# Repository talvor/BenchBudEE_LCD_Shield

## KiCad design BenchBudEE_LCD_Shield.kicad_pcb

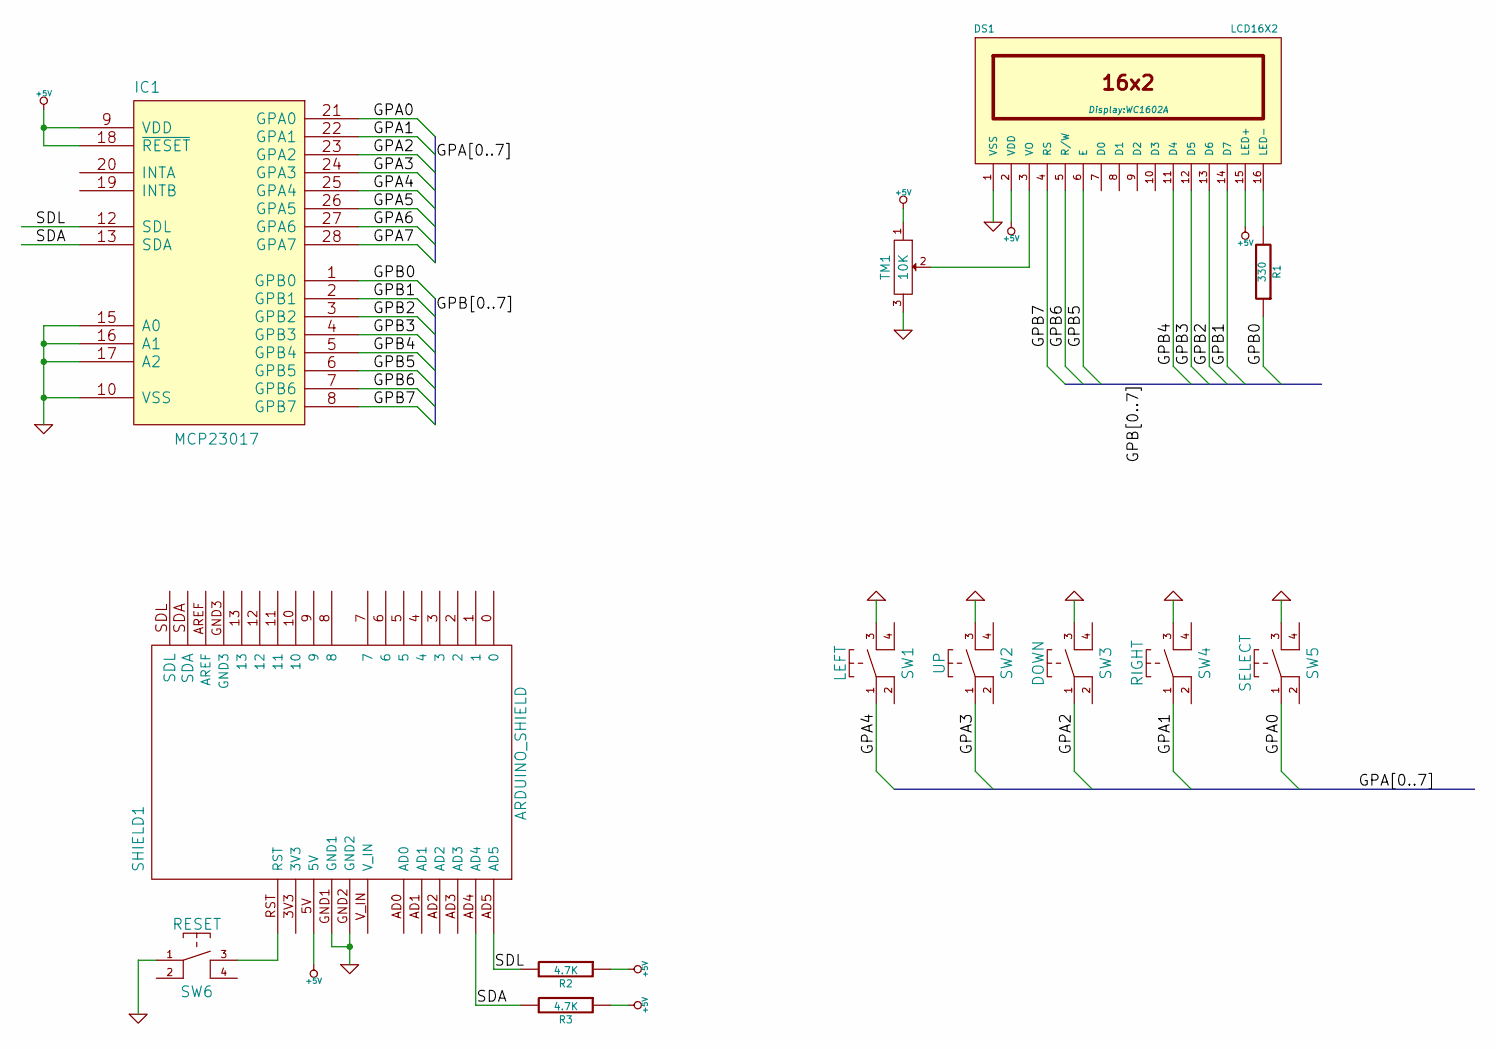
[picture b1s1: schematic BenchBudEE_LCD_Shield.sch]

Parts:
DS1: LCD16X2; WC1602A
IC1: MCP23017; SSOP-28; MFG Part Number MCP23017-E/SS
R1: 330; Resistor_SMD0805_HandSoldering
R2, R3: 4.7K; Resistor_SMD0805_HandSoldering
SHIELD1: ARDUINO_SHIELD; ARDUINO_UNO
SW1: LEFT; SW_PUSH; MFG Part Number MCDTS6-3R
SW2: UP; SW_PUSH; MFG Part Number MCDTS6-3R
SW3: DOWN; SW_PUSH; MFG Part Number MCDTS6-3R
SW4: RIGHT; SW_PUSH; MFG Part Number MCDTS6-3R
SW5: SELECT; SW_PUSH
SW6: RESET; SW_PUSH; MFG Part Number MCDTS6-3R
TM1: 10K; Potentiometer_VishaySpectrol-Econtrim-Type36k; MFG Part Number 3306P-1-103

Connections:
+5V: DS1.2 (VDD), DS1.15 (LED+), IC1.9 (VDD), IC1.18 (~RESET), R2.1, R3.1, SHIELD1.5V, TM1.1
/GPA0: IC1.21 (GPA0), SW5.1
/GPA1: IC1.22 (GPA1), SW4.1
/GPA2: IC1.23 (GPA2), SW3.1
/GPA3: IC1.24 (GPA3), SW2.1
/GPA4: IC1.25 (GPA4), SW1.1
/GPA5: IC1.26 (GPA5)
/GPA6: IC1.27 (GPA6)
/GPA7: IC1.28 (GPA7)
/GPB0: IC1.1 (GPB0), R1.1
/GPB1: DS1.14 (D7), IC1.2 (GPB1)
/GPB2: DS1.13 (D6), IC1.3 (GPB2)
/GPB3: DS1.12 (D5), IC1.4 (GPB3)
/GPB4: DS1.11 (D4), IC1.5 (GPB4)
/GPB5: DS1.6 (E), IC1.6 (GPB5)
/GPB6: DS1.5 (R/W), IC1.7 (GPB6)
/GPB7: DS1.4 (RS), IC1.8 (GPB7)
/SDA: IC1.13 (SDA), R3.2, SHIELD1.AD4
/SDL: IC1.12 (SDL), R2.2, SHIELD1.AD5
GND: DS1.1 (VSS), IC1.10 (VSS), IC1.15 (A0), IC1.16 (A1), IC1.17 (A2), SHIELD1.GND1, SHIELD1.GND2, SW1.3, SW2.3, SW3.3, SW4.3, SW5.3, SW6.1, TM1.3
unnamed: DS1.3 (VO), TM1.2
unnamed: DS1.16 (LED-), R1.2
unnamed: SHIELD1.RST, SW6.3

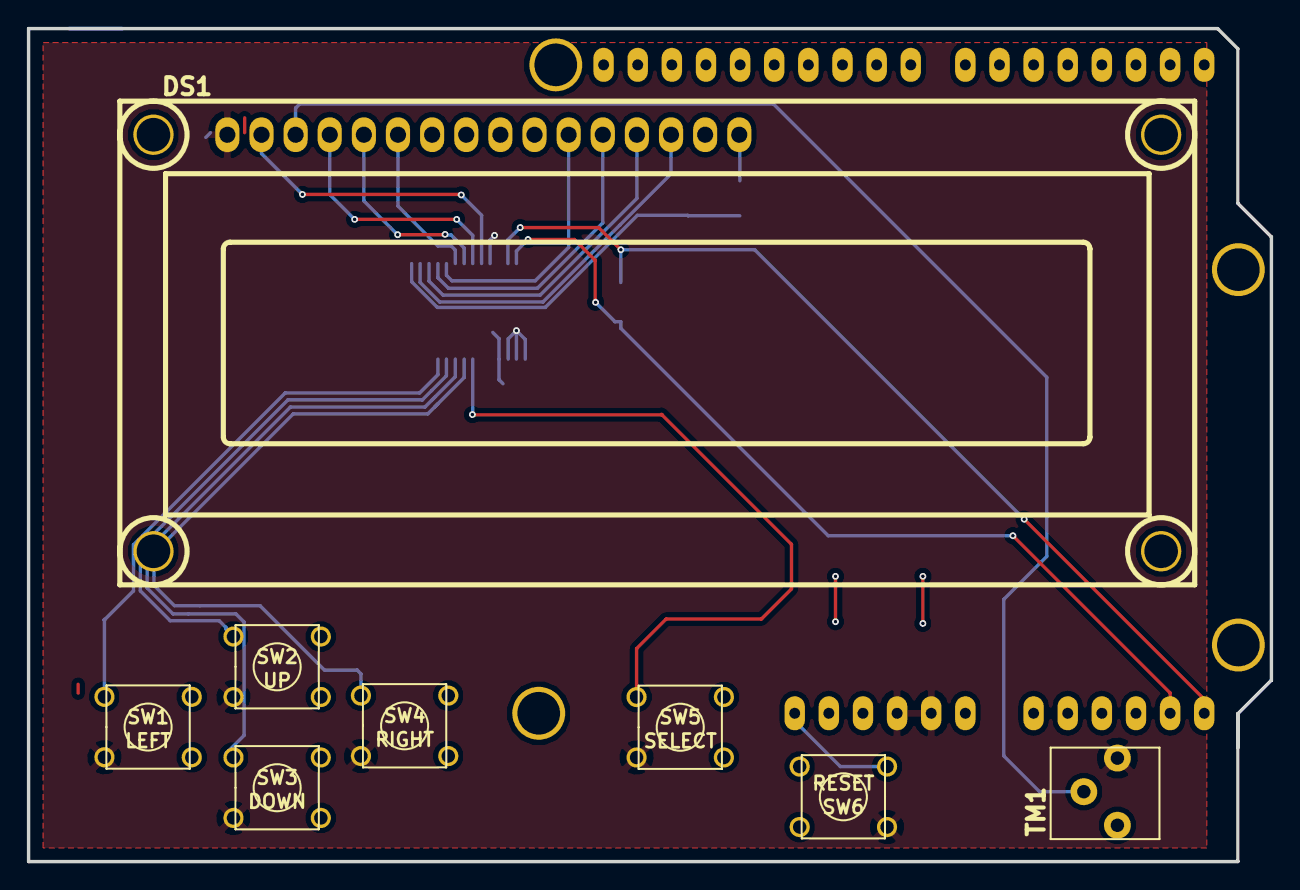
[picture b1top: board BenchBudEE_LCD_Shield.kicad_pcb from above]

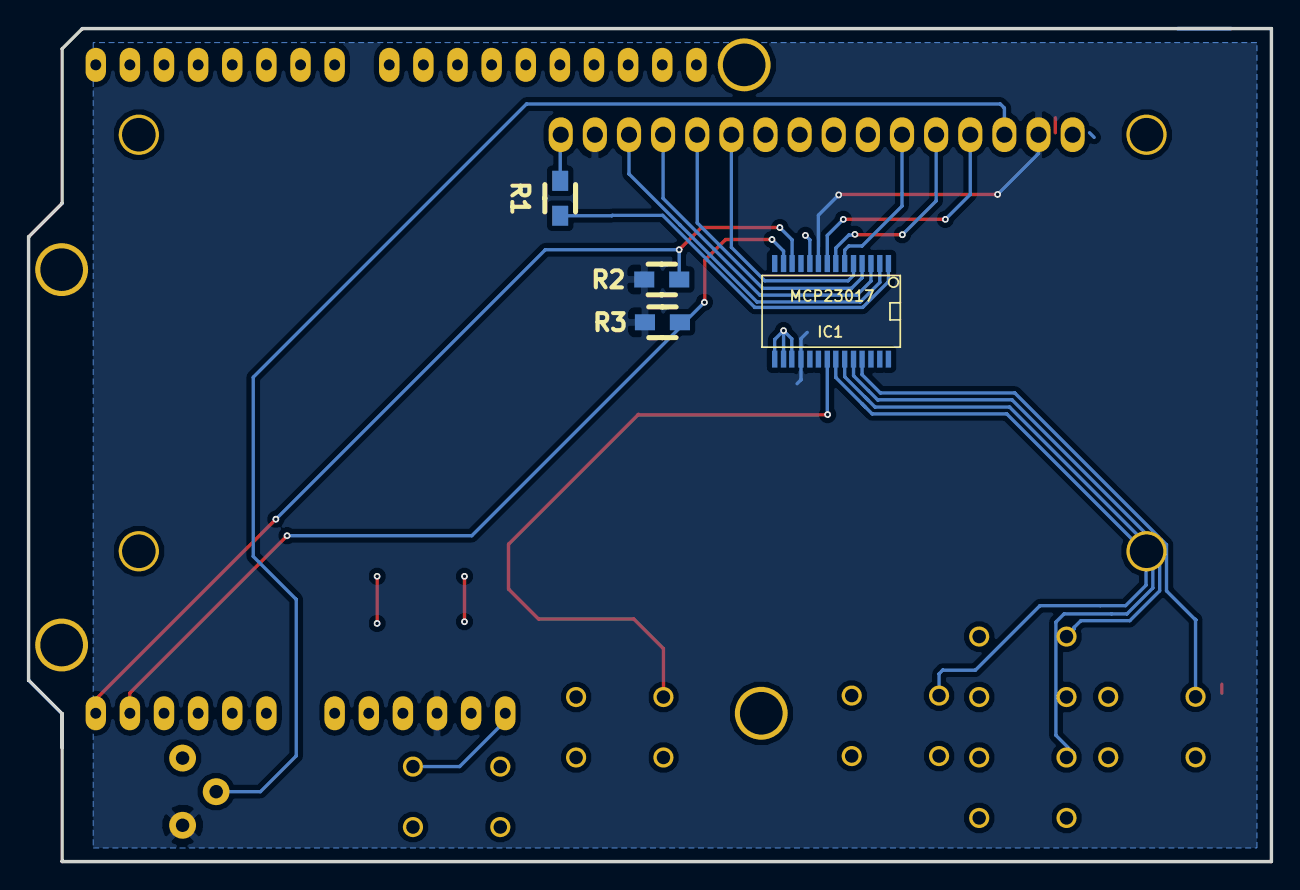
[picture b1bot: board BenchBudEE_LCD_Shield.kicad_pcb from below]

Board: 2 copper layers, 92.5 x 62.0 mm, 13 parts (4 on the bottom side), 20 nets.
